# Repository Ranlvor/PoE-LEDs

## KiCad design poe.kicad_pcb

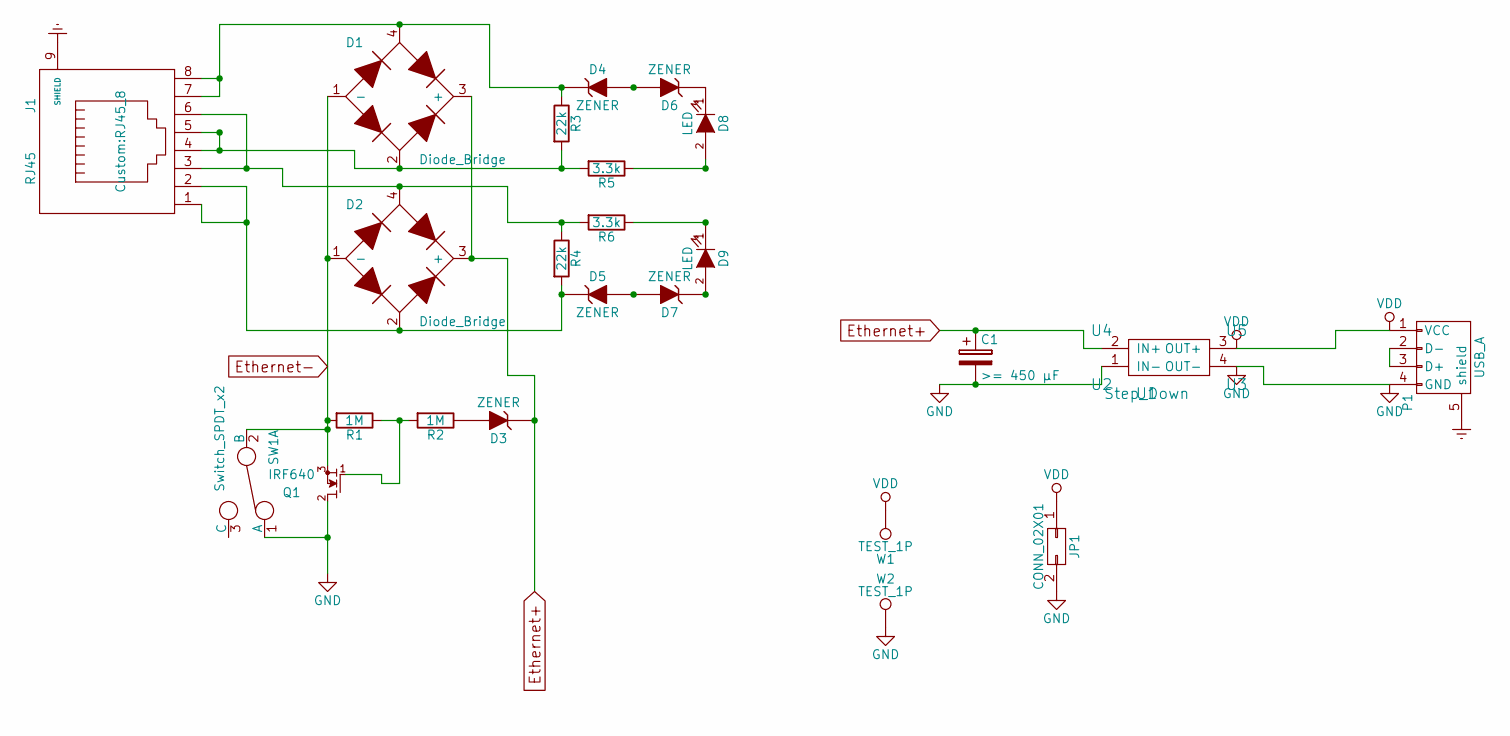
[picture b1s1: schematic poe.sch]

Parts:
C1: >= 450 µF; C2V8
D1, D2: Diode_Bridge; Diode-Bridge
D3, D4, D5, D6, D7: ZENER; D3
D8, D9: LED; LED-3MM
J1: RJ45; RJ45_8
JP1: CONN_02X01; 2-Jumper
P1: USB_A
Q1: IRF640; TO-220
R1, R2: 1M; Resistor_Horizontal_RM15mm
R3, R4: 22k; Resistor_Horizontal_RM15mm
R5, R6: 3.3k; Resistor_Horizontal_RM15mm
SW1: Switch_SPDT_x2; Switch
U1: Step_Down; Step-Down
U2, U3, U4, U5: Bananasocket
W1, W2: TEST_1P; 1x1cm-SMD-solderpad

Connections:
Earth: J1.9 (SHIELD), P1.5 (shield)
Ethernet+: C1.1, D1.3 (+), D2.3 (+), D3.1 (K), U1.2 (IN+), U4.1
Ethernet-: D1.1 (-), D2.1 (-), Q1.3 (S), R1.2, SW1.2 (B)
GND: C1.2, JP1.2, P1.4 (GND), Q1.2 (D), SW1.1 (A), U1.1 (IN-), U1.4 (OUT-), U2.1, U3.1, W2.1
unnamed: D1.2, J1.4, J1.5, R3.2, R5.2
unnamed: D1.4, D4.1 (K), J1.7, J1.8, R3.1
unnamed: D2.2, D5.1 (K), J1.1, J1.2, R4.2
unnamed: D2.4, J1.3, J1.6, R4.1, R6.2
unnamed: D3.2 (A), R2.1
unnamed: D4.2 (A), D6.2 (A)
unnamed: D5.2 (A), D7.2 (A)
unnamed: D6.1 (K), D8.1 (K)
unnamed: D7.1 (K), D9.2 (A)
unnamed: D8.2 (A), R5.1
unnamed: D9.1 (K), R6.1
unnamed: P1.2 (D-), P1.3 (D+)
unnamed: Q1.1 (G), R1.1, R2.2
VDD: JP1.1, P1.1 (VCC), U1.3 (OUT+), U5.1, W1.1

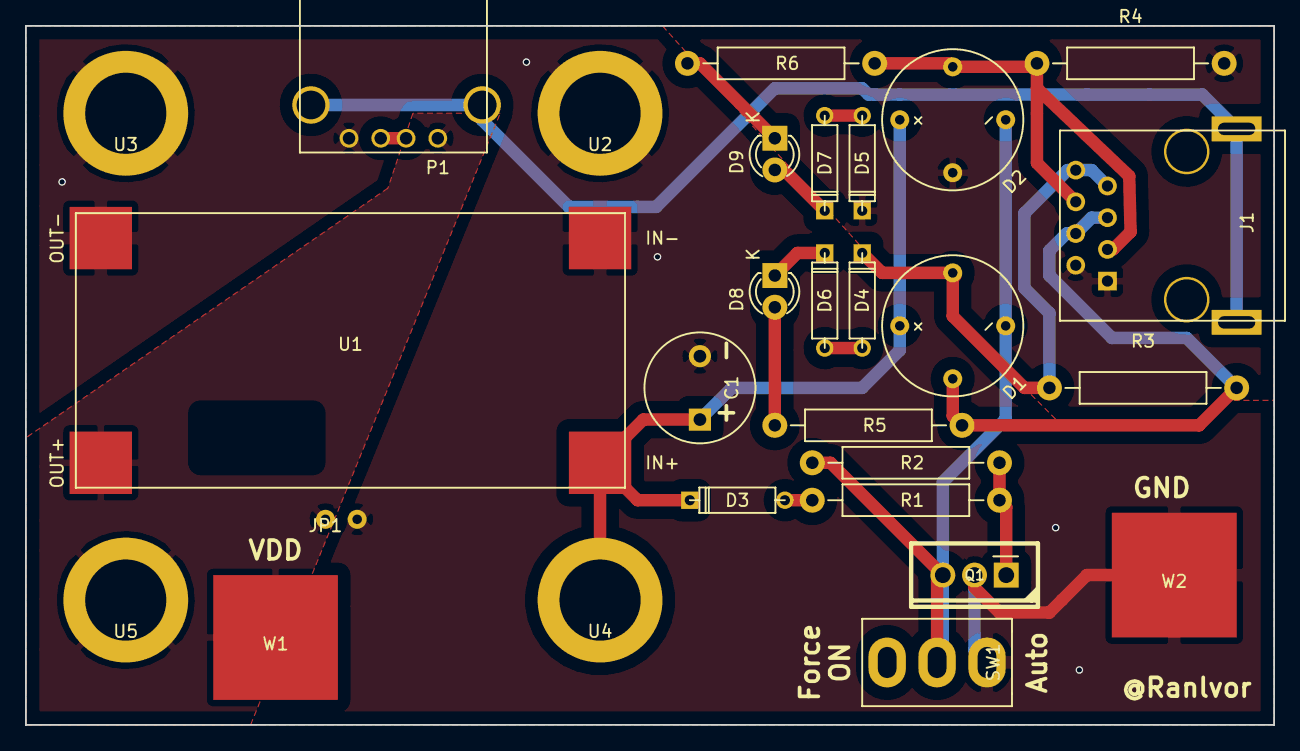
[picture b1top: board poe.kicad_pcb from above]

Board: 2 copper layers, 100.0 x 56.0 mm, 28 parts (0 on the bottom side), 18 nets.

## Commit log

2017-02-15 am Routing rumgespielt
2017-02-27 remove useless netlist
2017-02-27 Add NPN-MOSFET to output
2017-03-11 +NMOS/Zener-enable load after classification
2017-03-11 widerstände vereinheitlicht
2017-03-11 +notizen
2017-08-12 Stuff… Much Stuff…
    (i know this commit is bad… but it would have been necessary ages ago)
2019-10-24 various unknown changes
